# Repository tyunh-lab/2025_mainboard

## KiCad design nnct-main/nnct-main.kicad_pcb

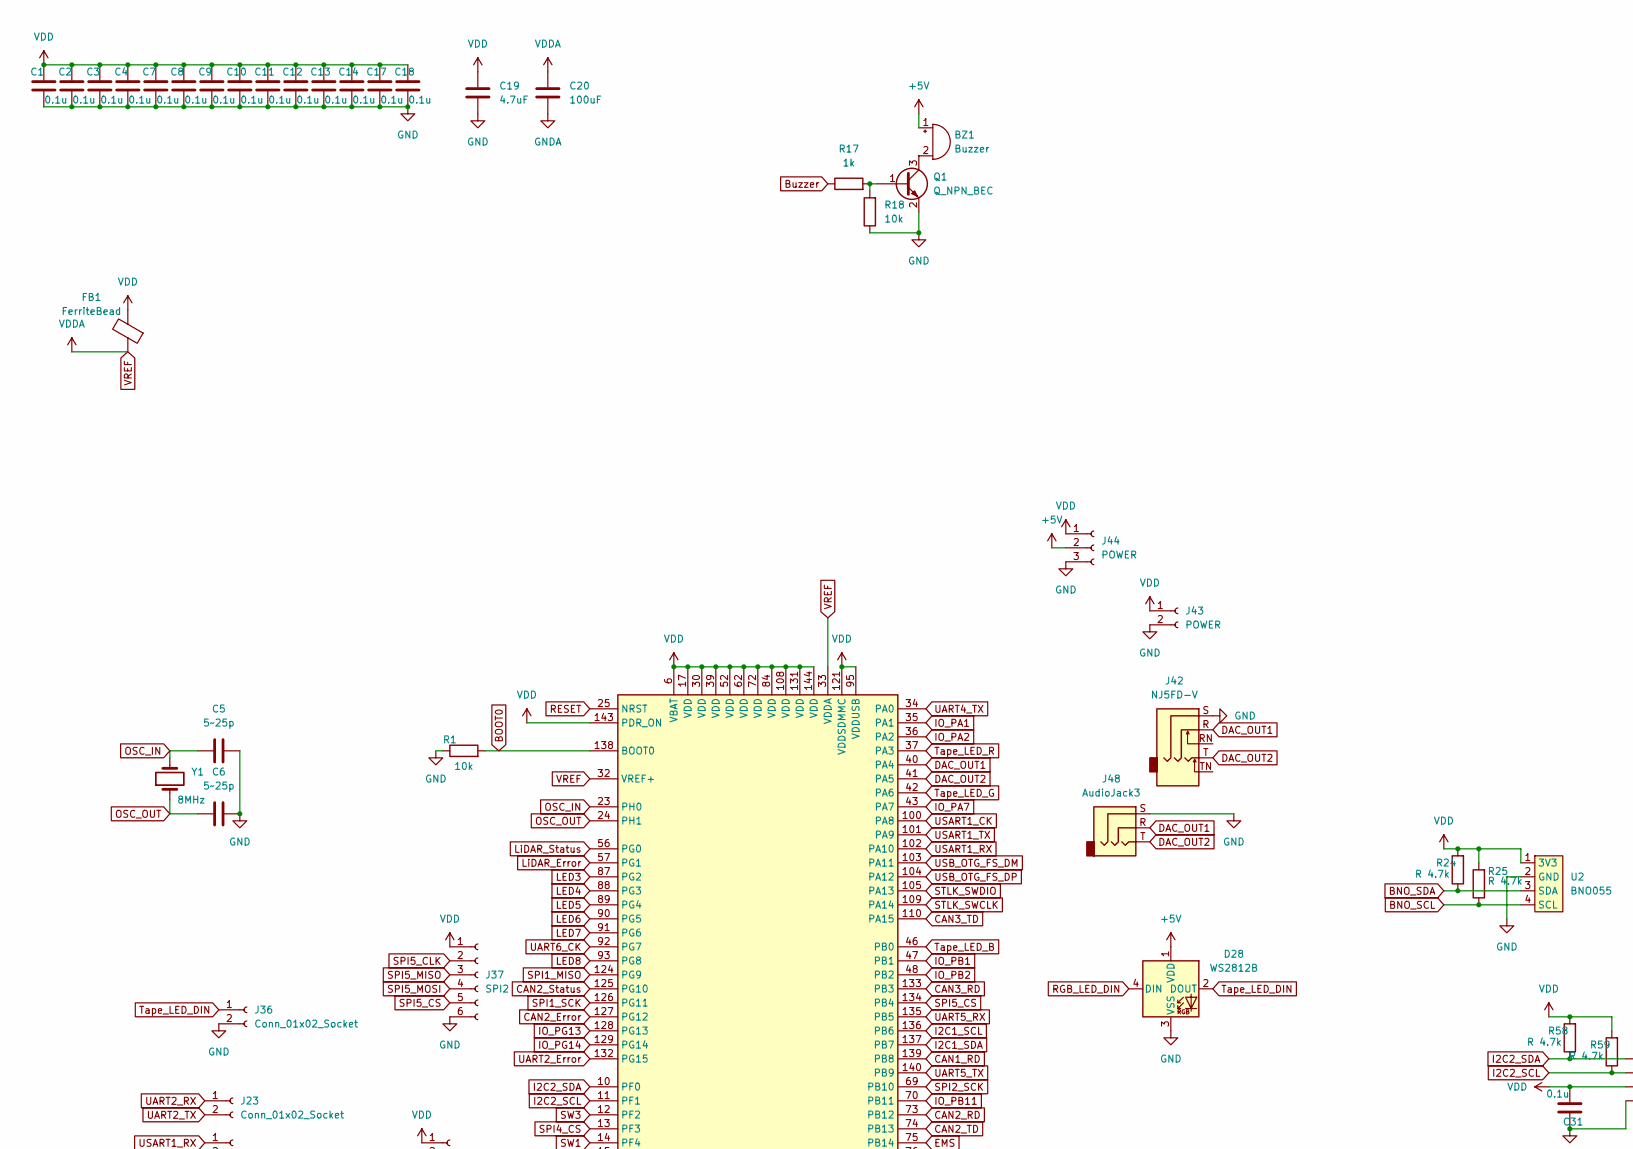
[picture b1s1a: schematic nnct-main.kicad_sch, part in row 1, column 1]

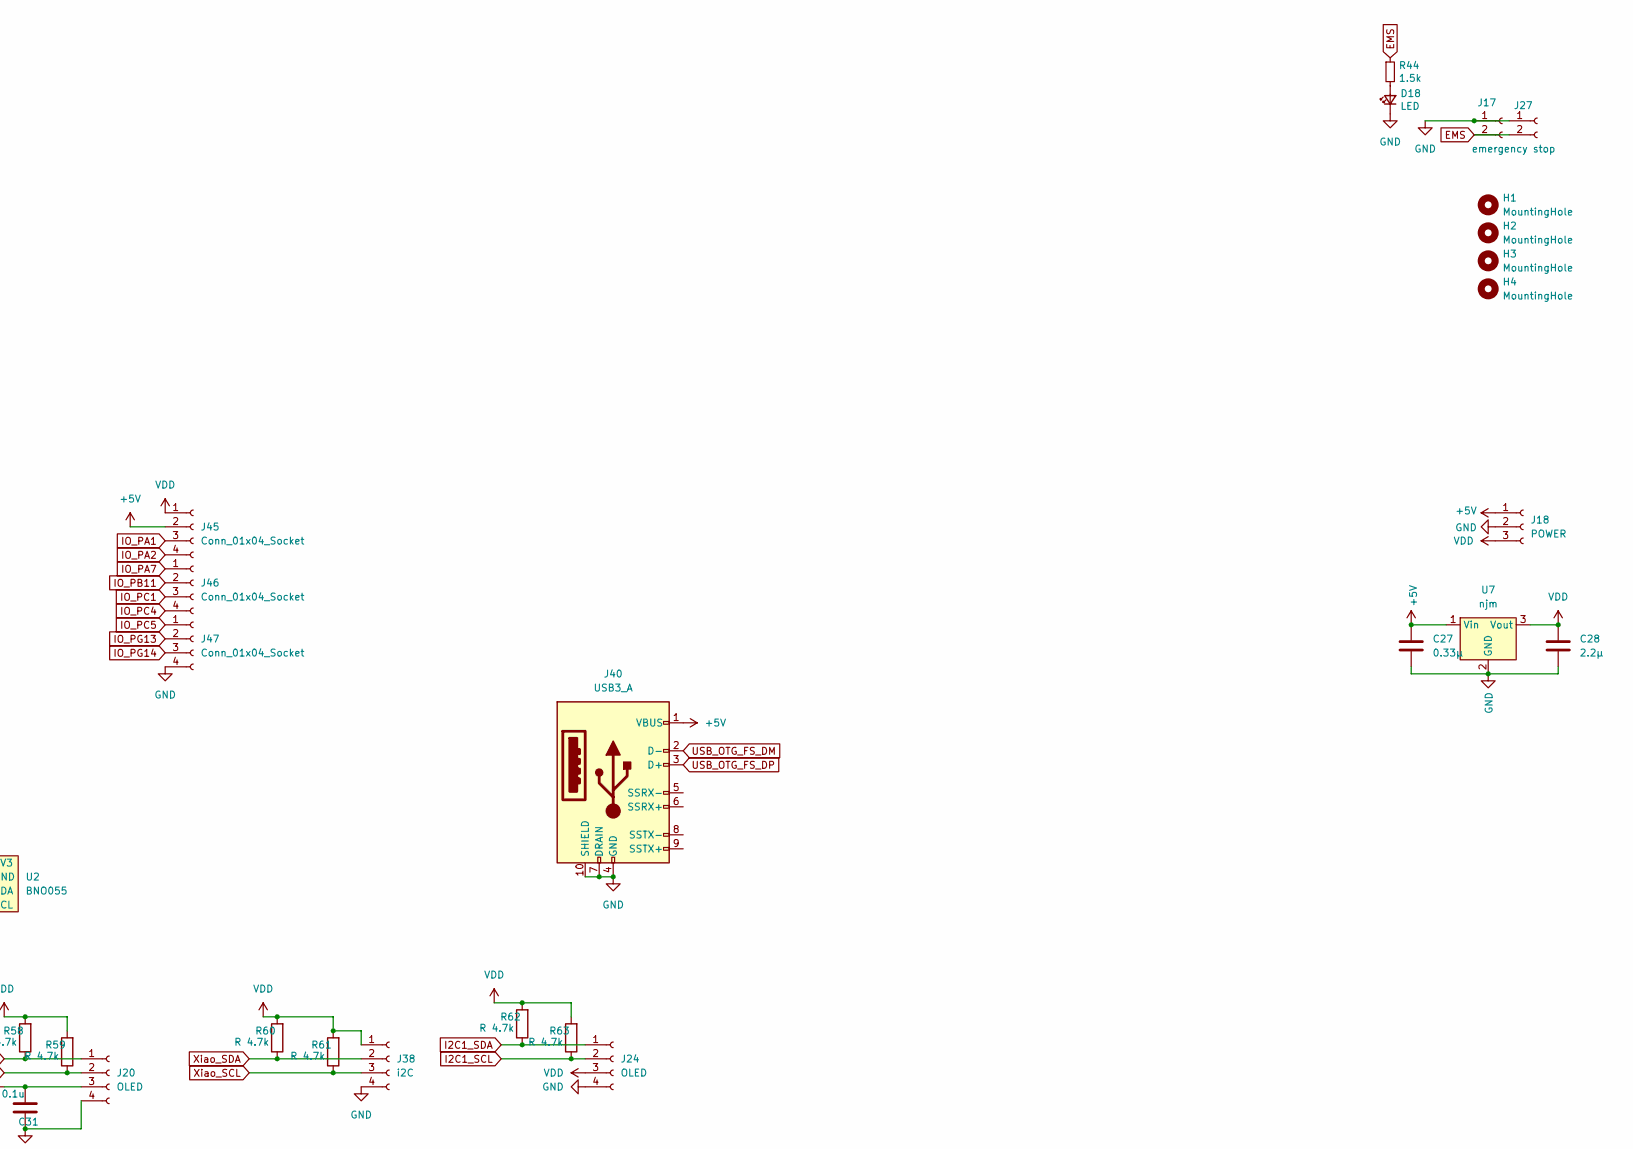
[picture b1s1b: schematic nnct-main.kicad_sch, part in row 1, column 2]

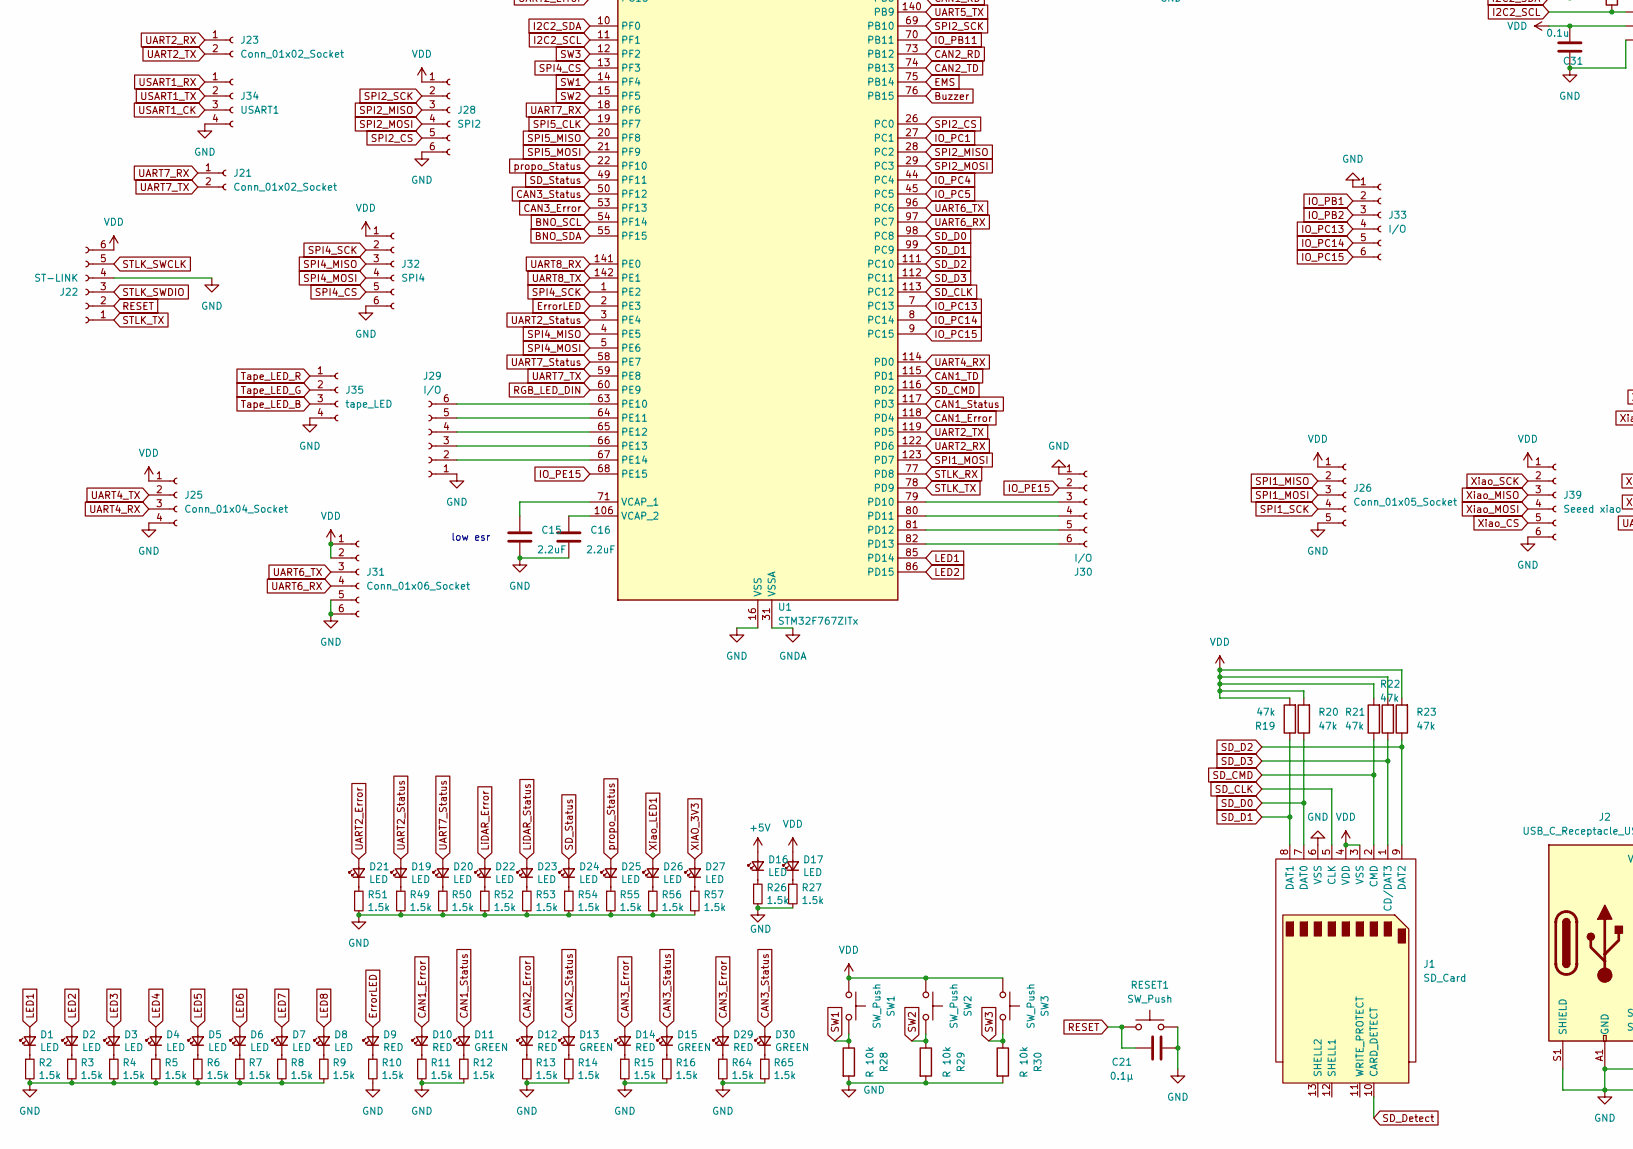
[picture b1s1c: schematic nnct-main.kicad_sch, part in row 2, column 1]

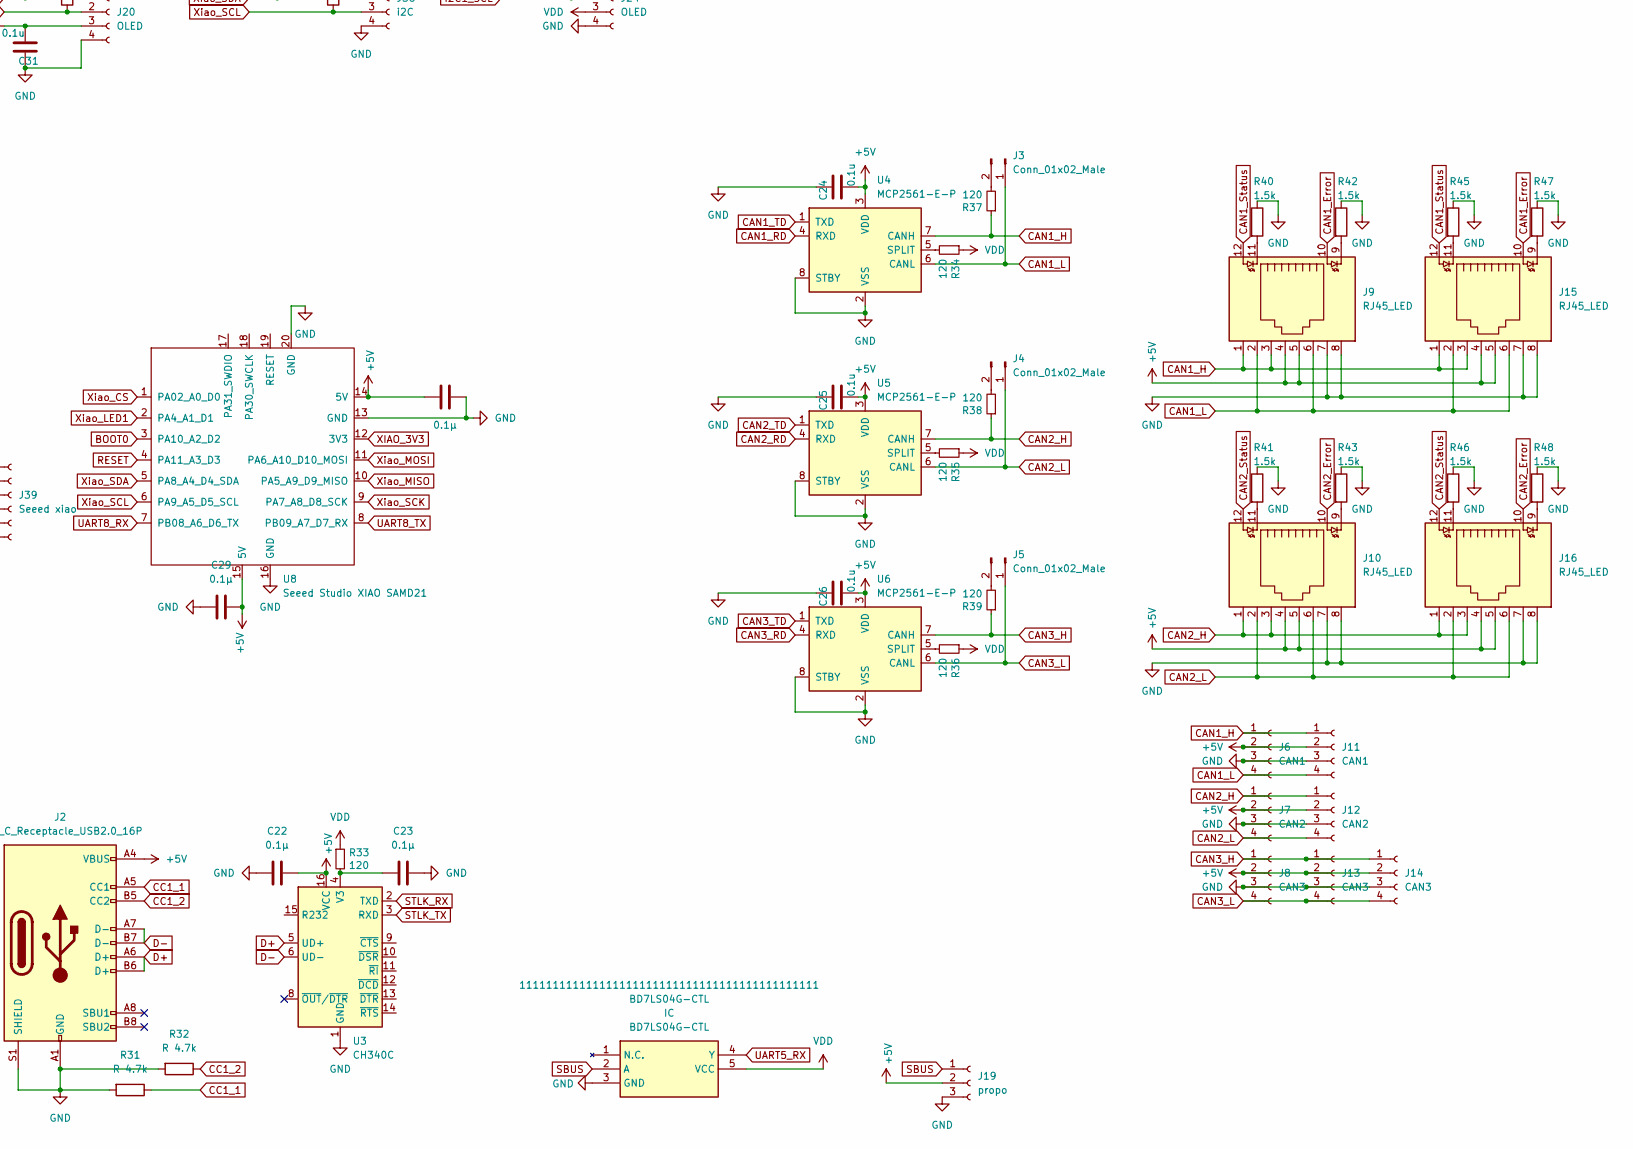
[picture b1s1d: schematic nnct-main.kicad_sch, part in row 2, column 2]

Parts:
111111111111111111111111111111111111111111111: BD7LS04G-CTL; SOT95P280X125-5N; Manufacturer_Part_Number BD7LS04G-CTL
BZ1: Buzzer; Buzzer_12x9.5RM7.6
C1, C2, C3, C4, C7, C8, C9, C10, C11, C12, C13, C14, C17, C18, C24, C25, C26, C31: 0.1u; C_0805_2012Metric_Pad1.18x1.45mm_HandSolder
C5, C6: 5~25p; C_0805_2012Metric_Pad1.18x1.45mm_HandSolder
C15, C16: 2.2uF; C_0805_2012Metric_Pad1.18x1.45mm_HandSolder
C19: 4.7uF; C_0805_2012Metric_Pad1.18x1.45mm_HandSolder
C20: 100uF; C_0805_2012Metric_Pad1.18x1.45mm_HandSolder
C21, C22, C23: 0.1µ; R_0805_2012Metric_Pad1.20x1.40mm_HandSolder
C27: 0.33µ; C_0805_2012Metric_Pad1.18x1.45mm_HandSolder
C28: 2.2µ; C_0805_2012Metric_Pad1.18x1.45mm_HandSolder
C29, C30: 0.1µ; C_0805_2012Metric_Pad1.18x1.45mm_HandSolder
D1, D2, D3, D4, D5, D6, D7, D8, D16, D17, D18, D19, D20, D21, D22, D23, D24, D25, D26, D27: LED; LED_0603_1608Metric_Pad1.05x0.95mm_HandSolder
D9, D10, D12, D14, D29: RED; LED_0603_1608Metric_Pad1.05x0.95mm_HandSolder
D11, D13, D15, D30: GREEN; LED_0603_1608Metric_Pad1.05x0.95mm_HandSolder
D28: WS2812B; LED_WS2812B_PLCC4_5.0x5.0mm_P3.2mm
FB1: FerriteBead; C_0805_2012Metric
H1, H2, H3, H4: MountingHole; MountingHole_3.2mm_M3_Pad_Via
J1: SD_Card; J_SD_Card-micro_socket_A
J2: USB_C_Receptacle_USB2.0_16P; USB_C_Receptacle_GCT_USB4105-xx-A_16P_TopMnt_Horizontal
J3, J4, J5: Conn_01x02_Male; PinHeader_1x02_P2.54mm_Vertical
J6, J11: CAN1; JST_GH_BM04B-GHS-TBT_1x04-1MP_P1.25mm_Vertical
J7, J12: CAN2; JST_GH_BM04B-GHS-TBT_1x04-1MP_P1.25mm_Vertical
J8, J13: CAN3; JST_GH_BM04B-GHS-TBT_1x04-1MP_P1.25mm_Vertical
J9, J10, J15, J16: RJ45_LED; RJ45_Amphenol_RJHSE538X
J14: CAN3; JST_GH_SM04B-GHS-TB_1x04-1MP_P1.25mm_Horizontal
J17: emergency stop; JST_XA_S02B-XASK-1_1x02_P2.50mm_Horizontal
J18: POWER; JST_XA_B03B-XASK-1_1x03_P2.50mm_Vertical
J19: propo; JST_XA_B03B-XASK-1_1x03_P2.50mm_Vertical
J20, J24: OLED; PinSocket_1x04_P2.54mm_Vertical
J21: Conn_01x02_Socket; JST_GH_SM02B-GHS-TB_1x02-1MP_P1.25mm_Horizontal
J22: ST-LINK; JST_GH_SM06B-GHS-TB_1x06-1MP_P1.25mm_Horizontal
J23, J36: Conn_01x02_Socket; JST_GH_BM02B-GHS-TBT_1x02-1MP_P1.25mm_Vertical
J25: Conn_01x04_Socket; PinSocket_1x04_P2.54mm_Vertical
J26: Conn_01x05_Socket; PinSocket_1x05_P2.54mm_Vertical
J27: emergency stop; JST_GH_BM02B-GHS-TBT_1x02-1MP_P1.25mm_Vertical
J28, J37: SPI2; JST_GH_BM06B-GHS-TBT_1x06-1MP_P1.25mm_Vertical
J29, J30, J33: I/O; JST_GH_BM06B-GHS-TBT_1x06-1MP_P1.25mm_Vertical
J31: Conn_01x06_Socket; PinHeader_1x06_P2.54mm_Vertical
J32: SPI4; JST_GH_BM06B-GHS-TBT_1x06-1MP_P1.25mm_Vertical
J34: USART1; JST_GH_BM04B-GHS-TBT_1x04-1MP_P1.25mm_Vertical
J35: tape_LED; JST_GH_BM04B-GHS-TBT_1x04-1MP_P1.25mm_Vertical
J38: i2C; JST_GH_BM04B-GHS-TBT_1x04-1MP_P1.25mm_Vertical
J39: Seeed xiao; JST_GH_BM06B-GHS-TBT_1x06-1MP_P1.25mm_Vertical
J40: USB3_A; USB_A_Molex_67643_Horizontal
J42: NJ5FD-V; Jack_6.35mm_Neutrik_NJ5FD-V_Vertical
J43: POWER; PinHeader_1x02_P2.54mm_Vertical
J44: POWER; PinHeader_1x03_P2.54mm_Vertical
J45, J46, J47: Conn_01x04_Socket; PinHeader_1x04_P2.54mm_Vertical
J48: AudioJack3; Jack_3.5mm_Lumberg_1503_07_Horizontal
Q1: Q_NPN_BEC; 2sc3265_SC-59_Handsoldering
R1, R18: 10k; R_0805_2012Metric_Pad1.20x1.40mm_HandSolder
R2, R3, R4, R5, R6, R7, R8, R9, R10, R11, R12, R13, R14, R15, R16, R26, R27, R40, R41, R42, R43, R44, R45, R46, R47, R48, R49, R50, R51, R52, R53, R54, R55, R56, R57, R64, R65: 1.5k; R_0805_2012Metric_Pad1.20x1.40mm_HandSolder
R17: 1k; R_0805_2012Metric_Pad1.20x1.40mm_HandSolder
R19, R20, R21, R22, R23: 47k; R_0805_2012Metric_Pad1.20x1.40mm_HandSolder
R24, R25, R31, R32, R58, R59, R60, R61, R62, R63: R 4.7k; R_0805_2012Metric_Pad1.20x1.40mm_HandSolder
R28, R29, R30: R 10k; R_0805_2012Metric_Pad1.20x1.40mm_HandSolder
R33, R37, R38, R39: 120; R_0805_2012Metric_Pad1.20x1.40mm_HandSolder
R34, R35, R36: 120; SolderJumper-2_P1.3mm_Open_TrianglePad1.0x1.5mm
RESET1: SW_Push; SW_PUSH_6mm
SW1, SW2, SW3: SW_Push; SW_PUSH_6mm
U1: STM32F767ZITx; LQFP-144_20x20mm_P0.5mm
U2: BNO055; bno055
U3: CH340C; SOIC-16_3.9x9.9mm_P1.27mm
U4, U5, U6: MCP2561-E-P; SOP-8_3.9x4.9mm_P1.27mm
U7: njm; NJM2845DL1-33
U8: Seeed Studio XIAO SAMD21; XIAO-ESP32-C6-DIP
Y1: 8MHz; crystal_hc-49u

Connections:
+5V: BZ1.1 (+), C22.2, C24.2, C25.2, C26.2, C27.2, C29.2, C30.2, D16.2 (A), D28.1 (VDD), J2.A4 (VBUS), J2.A9 (VBUS), J2.B4 (VBUS), J2.B9 (VBUS), J6.2, J7.2, J8.2, J9.4, J9.5, J10.4, J10.5, J11.2, J12.2, J13.2, J14.2, J15.4, J15.5, J16.4, J16.5, J18.1, J19.2, J40.1 (VBUS), J44.2, J45.2, U3.16 (VCC), U4.3 (VDD), U5.3 (VDD), U6.3 (VDD), U7.1 (Vin), U8.14 (5V), U8.15 (5V)
BNO_SCL: R25.1, U1.54 (PF14), U2.4 (SCL)
BNO_SDA: R24.1, U1.55 (PF15), U2.3 (SDA)
BOOT0: R1.2, U1.138 (BOOT0), U8.3 (PA10_A2_D2)
Buzzer: R17.1, U1.76 (PB15)
CAN1_Error: D10.2 (A), J9.10, J15.10, U1.118 (PD4)
CAN1_H: J6.1, J9.1, J9.3, J11.1, J15.1, J15.3, R37.1, U4.7 (CANH)
CAN1_L: J3.1, J6.4, J9.2, J9.6, J11.4, J15.2, J15.6, U4.6 (CANL)
CAN1_RD: U1.139 (PB8), U4.4 (RXD)
CAN1_Status: D11.2 (A), J9.12, J15.12, U1.117 (PD3)
CAN1_TD: U1.115 (PD1), U4.1 (TXD)
CAN2_Error: D12.2 (A), J10.10, J16.10, U1.127 (PG12)
CAN2_H: J7.1, J10.1, J10.3, J12.1, J16.1, J16.3, R38.1, U5.7 (CANH)
CAN2_L: J4.1, J7.4, J10.2, J10.6, J12.4, J16.2, J16.6, U5.6 (CANL)
CAN2_RD: U1.73 (PB12), U5.4 (RXD)
CAN2_Status: D13.2 (A), J10.12, J16.12, U1.125 (PG10)
CAN2_TD: U1.74 (PB13), U5.1 (TXD)
CAN3_Error: D14.2 (A), D29.2 (A), U1.53 (PF13)
CAN3_H: J8.1, J13.1, J14.1, R39.1, U6.7 (CANH)
CAN3_L: J5.1, J8.4, J13.4, J14.4, U6.6 (CANL)
CAN3_RD: U1.133 (PB3), U6.4 (RXD)
CAN3_Status: D15.2 (A), D30.2 (A), U1.50 (PF12)
CAN3_TD: U1.110 (PA15), U6.1 (TXD)
CC1_1: J2.A5 (CC1), R31.1
CC1_2: J2.B5 (CC2), R32.1
D+: J2.A6 (D+), J2.B6 (D+), U3.5 (UD+)
D-: J2.A7 (D-), J2.B7 (D-), U3.6 (UD-)
DAC_OUT1: J42.R, J48.R, U1.40 (PA4)
DAC_OUT2: J42.T, J48.T, U1.41 (PA5)
EMS: J17.2, J27.2, R44.1, U1.75 (PB14)
ErrorLED: D9.2 (A), U1.2 (PE3)
GND: 111111111111111111111111111111111111111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.3 (GND), C1.2, C2.2, C3.2, C4.2, C5.2, C6.2, C7.2, C8.2, C9.2, C10.2, C11.2, C12.2, C13.2, C14.2, C15.2, C16.2, C17.2, C18.2, C19.2, C21.2, C22.1, C23.2, C24.1, C25.1, C26.1, C27.1, C28.2, C29.1, C30.1, C31.1, D18.1 (K), D28.3 (VSS), J1.6 (VSS), J2.A1 (GND), J2.A12 (GND), J2.B1 (GND), J2.B12 (GND), J2.S1 (SHIELD), J6.3, J7.3, J8.3, J9.7, J9.8, J10.7, J10.8, J11.3, J12.3, J13.3, J14.3, J15.7, J15.8, J16.7, J16.8, J17.1, J18.2, J19.3, J20.4, J22.4, J24.4, J25.4, J26.5, J27.1, J28.6, J29.1, J30.1, J31.5, J31.6, J32.6, J33.1, J34.4, J35.4, J36.2, J37.6, J38.4, J39.6, J40.4 (GND), J40.7 (DRAIN), J40.10 (SHIELD), J42.S, J43.2, J44.3, J47.4, J48.S, Q1.2 (E), R1.1, R2.2, R3.2, R4.2, R5.2, R6.2, R7.2, R8.2, R9.2, R10.2, R11.2, R12.2, R13.2, R14.2, R15.2, R16.2, R18.1, R26.2, R27.2, R28.2, R29.2, R30.2, R31.2, R32.2, R40.1, R41.1, R42.1, R43.1, R45.1, R46.1, R47.1, R48.1, R49.2, R50.2, R51.2, R52.2, R53.2, R54.2, R55.2, R56.2, R57.2, R64.2, R65.2, RESET1.2, U1.16 (VSS), U1.38 (VSS), U1.51 (VSS), U1.61 (VSS), U1.83 (VSS), U1.94 (VSS), U1.107 (VSS), U1.120 (VSS), U1.130 (VSS), U2.2 (GND), U3.1 (GND), U4.2 (VSS), U4.8 (STBY), U5.2 (VSS), U5.8 (STBY), U6.2 (VSS), U6.8 (STBY), U7.2 (GND), U8.13 (GND), U8.16 (GND), U8.20 (GND)
GNDA: C20.2, U1.31 (VSSA)
I2C1_SCL: J24.2, R63.1, U1.136 (PB6)
I2C1_SDA: J24.1, R62.1, U1.137 (PB7)
I2C2_SCL: J20.2, R59.1, U1.11 (PF1)
I2C2_SDA: J20.1, R58.1, U1.10 (PF0)
IO_PA1: J45.3, U1.35 (PA1)
IO_PA2: J45.4, U1.36 (PA2)
IO_PA7: J46.1, U1.43 (PA7)
IO_PB1: J33.2, U1.47 (PB1)
IO_PB2: J33.3, U1.48 (PB2)
IO_PB11: J46.2, U1.70 (PB11)
IO_PC1: J46.3, U1.27 (PC1)
IO_PC4: J46.4, U1.44 (PC4)
IO_PC5: J47.1, U1.45 (PC5)
IO_PC13: J33.4, U1.7 (PC13)
IO_PC14: J33.5, U1.8 (PC14)
IO_PC15: J33.6, U1.9 (PC15)
IO_PE15: J30.2, U1.68 (PE15)
IO_PG13: J47.2, U1.128 (PG13)
IO_PG14: J47.3, U1.129 (PG14)
LED1: D1.2 (A), U1.85 (PD14)
LED2: D2.2 (A), U1.86 (PD15)
LED3: D3.2 (A), U1.87 (PG2)
LED4: D4.2 (A), U1.88 (PG3)
LED5: D5.2 (A), U1.89 (PG4)
LED6: D6.2 (A), U1.90 (PG5)
LED7: D7.2 (A), U1.91 (PG6)
LED8: D8.2 (A), U1.93 (PG8)
LiDAR_Error: D22.2 (A), U1.57 (PG1)
LiDAR_Status: D23.2 (A), U1.56 (PG0)
unnamed: BZ1.2 (-), Q1.3 (C)
unnamed: D1.1 (K), R2.1
unnamed: D2.1 (K), R3.1
unnamed: D3.1 (K), R4.1
unnamed: D4.1 (K), R5.1
unnamed: D5.1 (K), R6.1
unnamed: D6.1 (K), R7.1
unnamed: D7.1 (K), R8.1
unnamed: D8.1 (K), R9.1
unnamed: D9.1 (K), R10.1
unnamed: D10.1 (K), R11.1
unnamed: D11.1 (K), R12.1
unnamed: D12.1 (K), R13.1
unnamed: D13.1 (K), R14.1
unnamed: D14.1 (K), R15.1
unnamed: D15.1 (K), R16.1
unnamed: D16.1 (K), R26.1
unnamed: D17.1 (K), R27.1
unnamed: D18.2 (A), R44.2
unnamed: D19.1 (K), R49.1
unnamed: D20.1 (K), R50.1
unnamed: D21.1 (K), R51.1
unnamed: D22.1 (K), R52.1
unnamed: D23.1 (K), R53.1
unnamed: D24.1 (K), R54.1
unnamed: D25.1 (K), R55.1
unnamed: D26.1 (K), R56.1
unnamed: D27.1 (K), R57.1
unnamed: D29.1 (K), R64.1
unnamed: D30.1 (K), R65.1
unnamed: J3.2, R37.2
unnamed: J4.2, R38.2
unnamed: J5.2, R39.2
unnamed: J9.9, R42.2
unnamed: J9.11, R40.2
unnamed: J10.9, R43.2
unnamed: J10.11, R41.2
unnamed: J15.9, R47.2
unnamed: J15.11, R45.2
unnamed: J16.9, R48.2
unnamed: J16.11, R46.2
unnamed: J29.2, U1.67 (PE14)
unnamed: J29.3, U1.66 (PE13)
unnamed: J29.4, U1.65 (PE12)
unnamed: J29.5, U1.64 (PE11)
unnamed: J29.6, U1.63 (PE10)
unnamed: J30.3, U1.79 (PD10)
unnamed: J30.4, U1.80 (PD11)
unnamed: J30.5, U1.81 (PD12)
unnamed: J30.6, U1.82 (PD13)
unnamed: Q1.1 (B), R17.2, R18.2
unnamed: C15.1, U1.71 (VCAP_1)
unnamed: C16.1, U1.106 (VCAP_2)
unnamed: C23.1, R33.2, U3.4 (V3)
unnamed: R34.2, U4.5 (SPLIT)
unnamed: R35.2, U5.5 (SPLIT)
unnamed: R36.2, U6.5 (SPLIT)
OSC_IN: C5.1, U1.23 (PH0), Y1.2
OSC_OUT: C6.1, U1.24 (PH1), Y1.1
RESET: C21.1, J22.2, RESET1.1, U1.25 (NRST), U8.4 (PA11_A3_D3)
RGB_LED_DIN: D28.4 (DIN), U1.60 (PE9)
SBUS: 111111111111111111111111111111111111111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.2 (A), J19.1
SD_CLK: J1.5 (CLK), U1.113 (PC12)
SD_CMD: J1.2 (CMD), R21.1, U1.116 (PD2)
SD_D0: J1.7 (DAT0), R20.1, U1.98 (PC8)
SD_D1: J1.8 (DAT1), R19.1, U1.99 (PC9)
SD_D2: J1.9 (DAT2), R23.1, U1.111 (PC10)
SD_D3: J1.1 (CD/DAT3), R22.1, U1.112 (PC11)
SD_Status: D24.2 (A), U1.49 (PF11)
SPI1_MISO: J26.2, U1.124 (PG9)
SPI1_MOSI: J26.3, U1.123 (PD7)
SPI1_SCK: J26.4, U1.126 (PG11)
SPI2_CS: J28.5, U1.26 (PC0)
SPI2_MISO: J28.3, U1.28 (PC2)
SPI2_MOSI: J28.4, U1.29 (PC3)
SPI2_SCK: J28.2, U1.69 (PB10)
SPI4_CS: J32.5, U1.13 (PF3)
SPI4_MISO: J32.3, U1.4 (PE5)
SPI4_MOSI: J32.4, U1.5 (PE6)
SPI4_SCK: J32.2, U1.1 (PE2)
SPI5_CLK: J37.2, U1.19 (PF7)
SPI5_CS: J37.5, U1.134 (PB4)
SPI5_MISO: J37.3, U1.20 (PF8)
SPI5_MOSI: J37.4, U1.21 (PF9)
STLK_RX: U1.77 (PD8), U3.2 (TXD)
STLK_SWCLK: J22.5, U1.109 (PA14)
STLK_SWDIO: J22.3, U1.105 (PA13)
STLK_TX: J22.1, U1.78 (PD9), U3.3 (RXD)
SW1: R28.1, SW1.2, U1.14 (PF4)
SW2: R29.1, SW2.2, U1.15 (PF5)
SW3: R30.1, SW3.2, U1.12 (PF2)
Tape_LED_B: J35.3, U1.46 (PB0)
Tape_LED_DIN: D28.2 (DOUT), J36.1
Tape_LED_G: J35.2, U1.42 (PA6)
Tape_LED_R: J35.1, U1.37 (PA3)
UART2_Error: D21.2 (A), U1.132 (PG15)
UART2_RX: J23.1, U1.122 (PD6)
UART2_Status: D19.2 (A), U1.3 (PE4)
UART2_TX: J23.2, U1.119 (PD5)
UART4_RX: J25.3, U1.114 (PD0)
UART4_TX: J25.2, U1.34 (PA0)
UART5_RX: 111111111111111111111111111111111111111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.4 (Y), U1.135 (PB5)
UART5_TX: U1.140 (PB9)
UART6_CK: U1.92 (PG7)
UART6_RX: J31.4, U1.97 (PC7)
UART6_TX: J31.3, U1.96 (PC6)
UART7_RX: J21.1, U1.18 (PF6)
UART7_Status: D20.2 (A), U1.58 (PE7)
UART7_TX: J21.2, U1.59 (PE8)
UART8_RX: U1.141 (PE0), U8.7 (PB08_A6_D6_TX)
UART8_TX: U1.142 (PE1), U8.8 (PB09_A7_D7_RX)
USART1_CK: J34.3, U1.100 (PA8)
USART1_RX: J34.1, U1.102 (PA10)
USART1_TX: J34.2, U1.101 (PA9)
USB_OTG_FS_DM: J40.2 (D-), U1.103 (PA11)
USB_OTG_FS_DP: J40.3 (D+), U1.104 (PA12)
VDD: 111111111111111111111111111111111111111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.5 (VCC), C1.1, C2.1, C3.1, C4.1, C7.1, C8.1, C9.1, C10.1, C11.1, C12.1, C13.1, C14.1, C17.1, C18.1, C19.1, C28.1, C31.2, D17.2 (A), FB1.2, J1.3 (VSS), J1.4 (VDD), J18.3, J20.3, J22.6, J24.3, J25.1, J26.1, J28.1, J31.1, J31.2, J32.1, J37.1, J38.1, J39.1, J43.1, J44.1, J45.1, R19.2, R20.2, R21.2, R22.2, R23.2, R24.2, R25.2, R33.1, R34.1, R35.1, R36.1, R58.2, R59.2, R60.2, R61.2, R62.2, R63.2, SW1.1, SW2.1, SW3.1, U1.6 (VBAT), U1.17 (VDD), U1.30 (VDD), U1.39 (VDD), U1.52 (VDD), U1.62 (VDD), U1.72 (VDD), U1.84 (VDD), U1.95 (VDDUSB), U1.108 (VDD), U1.121 (VDDSDMMC), U1.131 (VDD), U1.143 (PDR_ON), U1.144 (VDD), U2.1 (3V3), U7.3 (Vout)
VREF: C20.1, FB1.1, U1.32 (VREF+), U1.33 (VDDA)
XIAO_3V3: D27.2 (A), U8.12 (3V3)
Xiao_CS: J39.5, U8.1 (PA02_A0_D0)
Xiao_LED1: D26.2 (A), U8.2 (PA4_A1_D1)
Xiao_MISO: J39.3, U8.10 (PA5_A9_D9_MISO)
Xiao_MOSI: J39.4, U8.11 (PA6_A10_D10_MOSI)
Xiao_SCK: J39.2, U8.9 (PA7_A8_D8_SCK)
Xiao_SCL: J38.3, R61.1, U8.6 (PA9_A5_D5_SCL)
Xiao_SDA: J38.2, R60.1, U8.5 (PA8_A4_D4_SDA)
propo_Status: D25.2 (A), U1.22 (PF10)

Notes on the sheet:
low esr

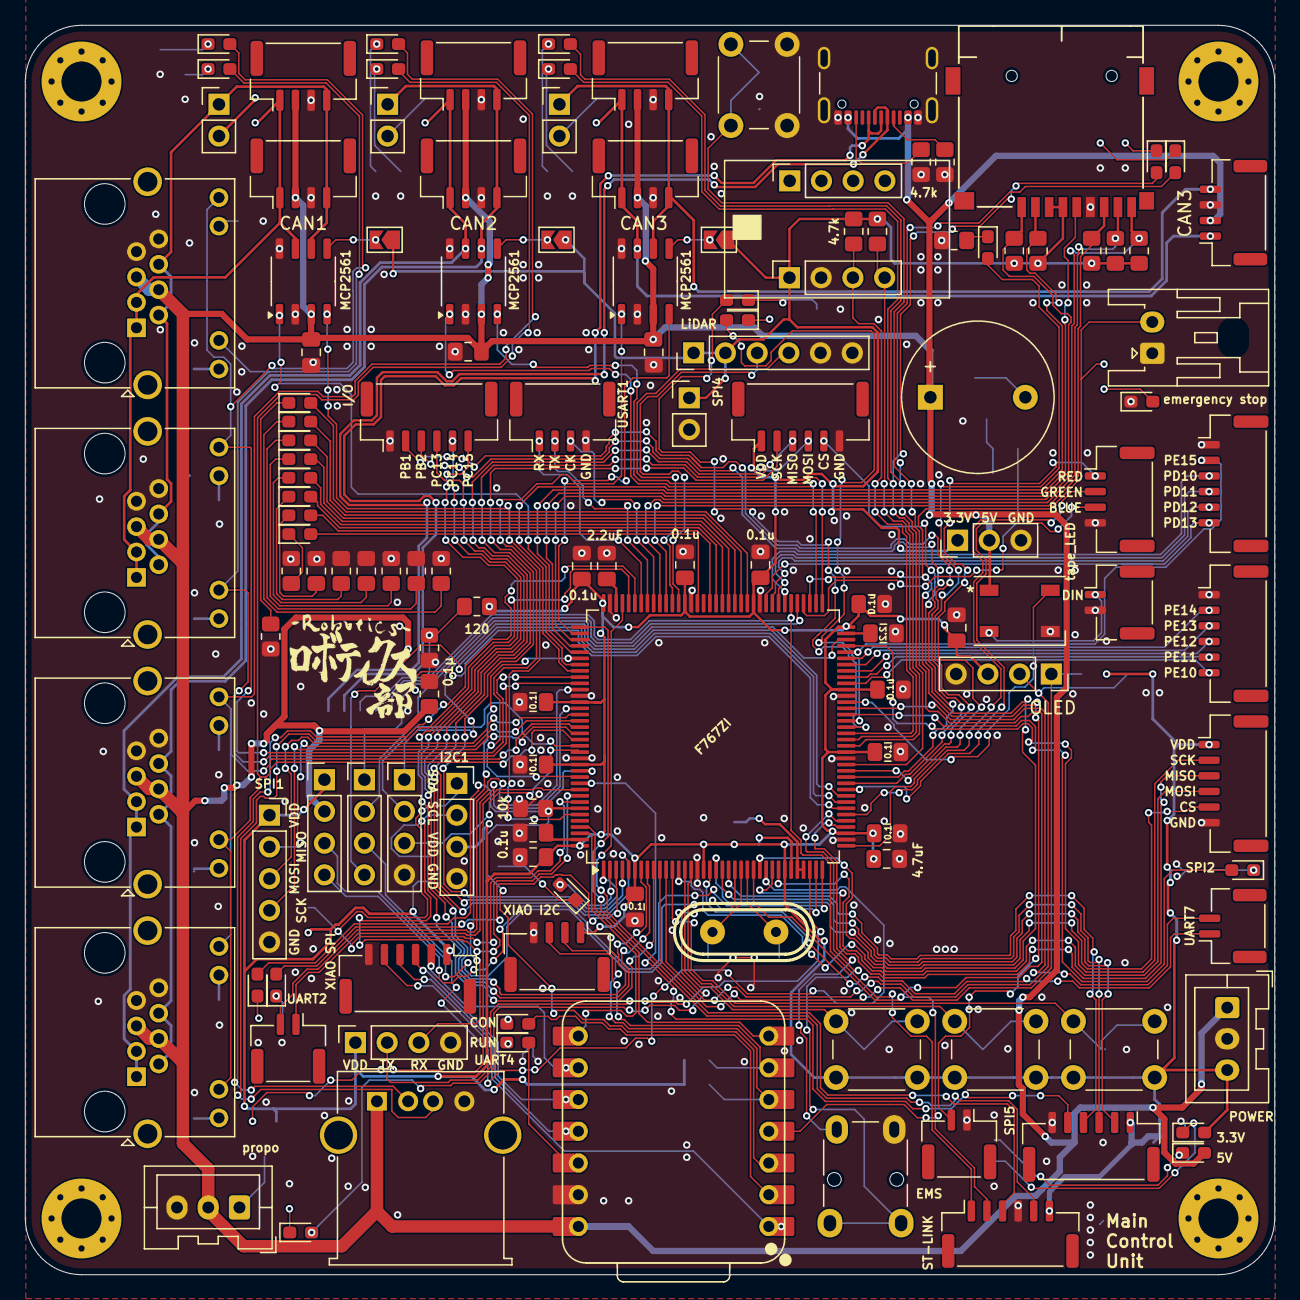
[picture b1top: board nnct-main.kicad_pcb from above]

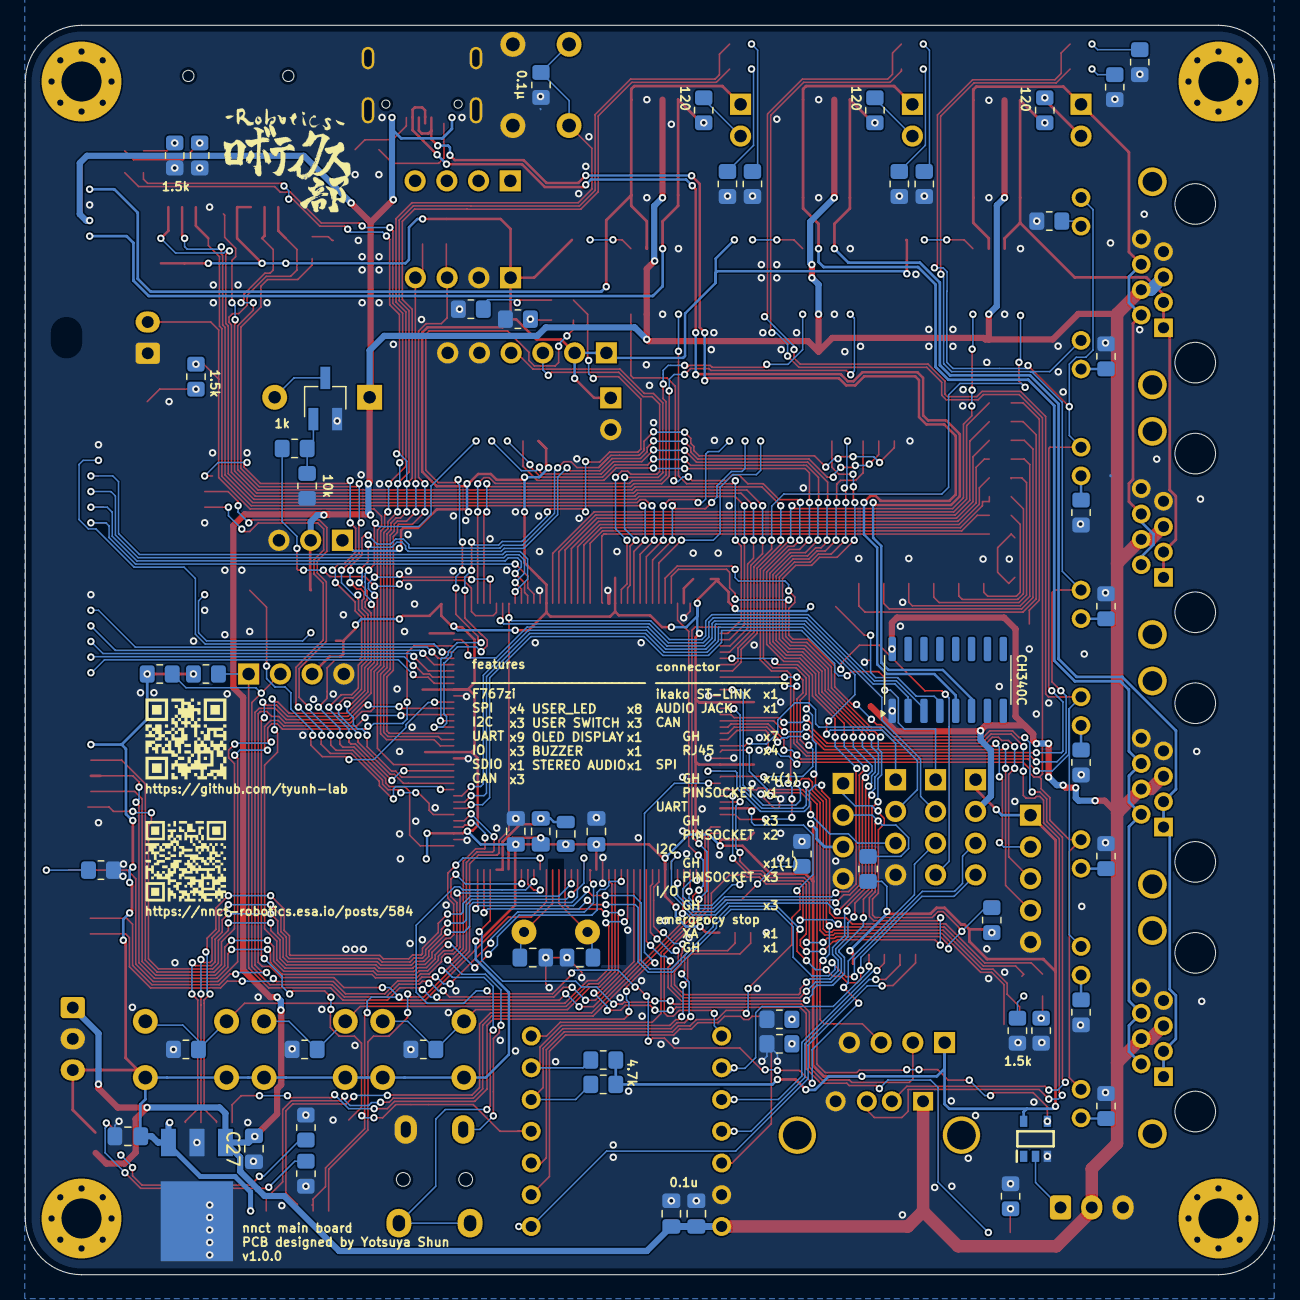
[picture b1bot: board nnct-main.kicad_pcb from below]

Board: 2 copper layers, 100.0 x 100.0 mm, 193 parts (57 on the bottom side), 187 nets.
